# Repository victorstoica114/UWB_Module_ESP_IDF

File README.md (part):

# UWB ESP-IDF

ESP-IDF 6.0.2 firmware for the custom UWB Module V1.0 Rev.B, based on an
ESP32-S3-WROOM-1-N16R8. The same application image runs on every module;
persistent identity and runtime configuration select the role and active
workflow on each board.

The current firmware combines DW3000 positioning, PX1105R GNSS/RTK, BNO085
IMU telemetry, BQ25792 charging, MAX77958 USB-C Power Delivery, authenticated
HTTP OTA/configuration, a browser dashboard, and boot-loop/OTA recovery. The
UWB radio runtimes include Native DS-TWR, FlexTDOA, Passive DS-TWR, calibration,
survey, distance-test, and beacon diagnostics.

Current firmware defaults, before an NVS override is loaded:

| Setting | Default |
| --- | --- |
| Runtime | `uwb_ranging` (Native DS-TWR) |
| UWB | enabled |
| BNO085 | disabled; `2 ms` / 500 Hz requested when enabled |
| PX1105R GNSS | disabled |
| BQ25792 monitor | enabled, nominal 1 Hz refresh |
| MAX77958 monitor | enabled, nominal 1 Hz refresh |
| Wi-Fi logs / binary telemetry | enabled |
| Storage | 16 MB flash, dual 4 MB OTA slots, 8 MB octal PSRAM |

Wi-Fi credentials, the OTA token, and optional NTRIP credentials are read from
the Git-ignored `secrets.h`. Copy `secrets.example.h` as the starting template.
Non-secret defaults live in `components/config`; authenticated runtime
overrides are stored in ESP32 NVS.

## Documentation Map

- Hardware, firmware ownership, boot order, and tasks are documented below in
  [Hardware](#hardware) and [Firmware Architecture](#firmware-architecture).
- UWB modes and packet/timing details start at [App Modes](#app-modes) and
  [UWB Ranging Protocol](#uwb-ranging-protocol). Passive DS-TWR and the clean
  FlexTDOA implementation also have dedicated notes in
  [`docs/PASSIVE_DS_TWR.md`](docs/PASSIVE_DS_TWR.md) and
  [`docs/FLEXTDOA_CLEAN_REIMPLEMENTATION.md`](docs/FLEXTDOA_CLEAN_REIMPLEMENTATION.md).
- Operator controls are grouped under [HTTP Control Surface](#http-control-surface),
  [BNO085 IMU](#bno085-imu), [BQ25792 Battery Charger](#bq25792-battery-charger),
  and [MAX77958 USB-C PD Controller](#max77958-usb-c-pd-controller).
- Build, serial flash, OTA, dashboard, and host-test commands are under
  [Local Workflow, Flashing, and VS Code Tasks](#local-workflow-flashing-and-vs-code-tasks).
- Released ESP32 images are on the
  [GitHub Releases page](https://github.com/victorstoica114/UWB_Module_ESP_IDF/releases),
  while the separately versioned GNSS image is indexed in
  [`PX1105R-firmware/README.md`](PX1105R-firmware/README.md).
- Final reports and their retained evidence bundles are indexed in
  [`reports/README.md`](reports/README.md).
- The parametric enclosure sources, print-ready STL files, STEP exports, and
  assembly notes are under
  [`mechanical/uwb-gps-enclosure/`](mechanical/uwb-gps-enclosure/README.md).

## Hardware

This firmware targets the custom UWB Module V1.0 Rev.B hardware.

| Area | Details |
| --- | --- |
| MCU | ESP32-S3-WROOM-1-N16R8 |
| Flash / PSRAM | 16 MB flash, 8 MB PSRAM |
| USB | Native USB CDC on boot |
| UWB | DW3000/DWM3000 radio path |
| IMU | BNO085 over shared I2C |
| GPS | PX1105R/PX1125R-class GPS path |
| USB-C / PD | MAX77958 |
| Charger | BQ25792 |
| Status LED | GPIO42, active-high |

Active pin mapping lives in `components/config/include/board_config.h`.

| Function | GPIO |
| --- | --- |
| Status LED | `42` |
| Shared I2C SDA / SCL | `9` / `10` |
| BNO085 reset / interrupt | `40` / `15` |
| BQ25792 interrupt / QON command / board PG | `4` / `38` / `5` |
| UWB reset / IRQ / CS / wakeup | `8` / `6` / `48` / `7` |
| SPI MOSI / SCK / MISO | `11` / `12` / `13` |
| GPS enable / RX / TX | `47` / `18` / `17` |
| GNSS correction UART TX | `1` |

### DW3000 SPI Clock

The DWM3000 data sheet specifies a maximum SPI clock of `38 MHz` in mode 0
after OTP boot has completed. ESP32-S3 SPI2 is sourced from the `80 MHz` APB
clock and can generate `40 MHz` exactly. This project deliberately selects
that divider after field validation on all five modules. It is a documented
2 MHz overclock, guarded by an explicit compile-time opt-in and a separate
`38 MHz` data-sheet-limit constant so the exception cannot be accidental.

The driver therefore uses two phases:

1. reset, `DEV_ID` probe, soft reset, OTP reads, and radio configuration at
   `4 MHz`;
2. operational RX/TX traffic requested and realized at `40 MHz`, after eight
   consecutive `DEV_ID` read-backs succeed.

If the operational verification fails, the driver automatically restores the
`4 MHz` device configuration so the module remains reachable. `/status`
exposes the effective value as `uwb_spi_clock_hz`; this is the frequency
reported by the ESP-IDF SPI driver, not only the requested value.

Hardware validation on all five modules, updated 2026-08-05:

| Metric | Result |
| --- | ---: |
| Effective SPI clock, every module | `40 MHz` |
| Pure CI-CR validation window | `35 s` |
| Selected slot / four-anchor frame | `4.80 ms / 19.20 ms` |
| Passive observations | `443-450/s` |
| Telemetry drops | `0` |
| Responder-index balance per anchor | typically `37-39 / 37-39 / 37-39` per second |
| Rejected tag observations | typically `0-1/s` |
| Incoherent anchor timestamps in stable windows | `0` |

The radio test exercises TX-buffer writes, delayed-TX programming, timestamp
and status reads, and RX-buffer reads. It is therefore a stronger link check
than probing `DEV_ID` alone.

## Firmware Architecture

`main/app_main.c` only calls `app_manager_start()`. The application manager
initializes identity and runtime configuration, brings up the recovery/control
plane first, and then starts hardware services and exactly one UWB runtime.

| Component | Responsibility |
| --- | --- |
| `app_manager` | Boot sequencing, status LED, recovery cutoff, and active-runtime selection. |
| `config` | Board pins, compile-time defaults, persistent module identity/antenna delay, and NVS runtime configuration. |
| `boot_guard` | ESP-IDF OTA validation plus RTC-memory crash-loop detection and recovery mode. |
| `wifi_service` | STA scan, connection, reconnect, BSSID/channel diagnostics, and network status. |
| `ota_service` | HTTP server, `/status`, OTA, GNSS update staging, and authenticated configuration endpoints. |
| `wireless_log_service` | TCP mirror of ESP-IDF text logs. |
| `wireless_telemetry_service` | Batched `UWT1` binary sensor, geometry, range, and position streams. |
| `resource_monitor_service` | Bounded RAM, PSRAM, flash, temperature, and per-core CPU diagnostics. |
| `i2c_bus_service` | Shared BNO085 realtime/BQ25792/MAX77958 background arbitration and optional SCL measurement. |
| `bno085_service` | Interrupt-driven accelerometer and GyroRV acquisition, timestamp reconstruction, recovery, rings, and telemetry. |
| `charger_service` | BQ25792 monitoring, decoded status/ADC data, controlled writes, and NVS-backed charger policy. |
| `max77958_service` | MAX77958 status, AP commands, optional direct-HS I2C, PDO/PPS control, and NVS-backed PD policy. |
| `gps_service` | PX1105R power/UART control, NMEA/SkyTraq parsing, 8 Hz setup, moving-base transport, and NTRIP. |
| `gnss_firmware_updater` | Fixed PX1105R loader/image update sequence using ESP32 PSRAM staging. |
| `uwb_dw3000` | DW3000 GPIO/SPI/IRQ ownership and all timing-critical UWB runtime loops. |
| `uwb_ranging_service` | Native DS-TWR positioning entry point. |
| `uwb_distance_test_service` | Two-module five-frame diagnostic DS-TWR entry point. |
| `uwb_calibration_service` | Two- and three-module antenna-delay calibration entry point. |
| `uwb_anchor_survey_service` | Anchor-to-anchor survey entry point. |
| `flextdoa_protocol` | FlexTDOA packet codec, collector, and CFO estimator. |
| `flextdoa_algmin` | FlexTDOA frame aggregation and 2D minimization. |
| `flextdoa_solver_service` | Asynchronous embedded FlexTDOA solver and position publication. |
| `passive_ds_solver_service` | Passive DS batching, dynamic geometry, correlated solve, and position publication. |
| `uwb_mobile_geometry` | Converts GNSS anchor positions into a shared local UWB coordinate frame. |
| `uwb_localization_solver` | Generic tested range/range-difference solver library; it is not the owner of a current runtime loop. |

Repository-level supporting material:

| Path | Contents |
| --- | --- |
| `tools/` | Build/OTA helpers, dashboard, listeners, capture, replay, calibration, and analysis tools. |
| `tests/` | Python host tests and standalone C algorithm/protocol tests. |
| `docs/` | Focused protocol and implementation notes. |
| `firmware_images/` | Retained ESP32 release inputs, stored through Git LFS where configured. |
| `PX1105R-firmware/` | Permanent GNSS firmware index and validated ESP32-assisted update artifacts. |
| `reports/` | Final PDFs plus one self-contained evidence bundle for each report. |
| `mechanical/uwb-gps-enclosure/` | Parametric V4 enclosure source, reference geometry, print-ready STL files, STEP exports, and previews. |
| `PCB/V1.REV.B/` | KiCad source, fabrication, BOM, and placement package. |
| `Schematic/` / `datasheets/` | Exported board schematic and local silicon/reference documents. |
| `reference/` | Migration notes and the intentionally retained legacy GPIO header. |

`components/config/include/board_config.h` is the active board pin map.
Old GPIO naming is kept only under `reference/legacy_headers`.
Old legacy project files and cloned third-party repositories are kept local for
inspiration/debugging and are intentionally ignored by Git.

`components/config/include/app_config.h` holds versioned non-secret application
settings: the default runtime mode, persistent identity provisioning, Wi-Fi
diagnostics/reconnect behavior, wireless-log defaults, OTA-adjacent
service defaults, and optional sensor-test parameters. `components/config/include/uwb_config.h`
holds UWB-only settings: role, source ID override, antenna delay, beacon
smoke-test parameters, and runtime defaults. Runtime overrides are stored in
NVS through `/config/runtime`. Keep Wi-Fi credentials and OTA tokens in
`secrets.h`.

Runtime ownership is intentionally narrow:

- `main/app_main.c` only boots the firmware and calls `app_manager_start()`.
- `components/app_manager/app_manager.c` owns what runs on the board and in
  what order.
- Long-lived workflows live in separate services/components, then are selected
  or sequenced by `app_manager`.

The current boot sequence is also explicit. `app_manager` starts the status LED
and boot guard, loads identity/runtime configuration, then brings up Wi-Fi,
wireless logs, binary telemetry, and the HTTP/OTA server. It schedules stable
boot confirmation only after that recovery/control plane is reachable. A normal
boot then starts the resource monitor, optional GNSS, the selected UWB runtime,
BQ25792, MAX77958, and finally the optional BNO085 service. Recovery mode stops
before that second group and holds the DW3000 in reset.

The application task/core split is kept simple so the UWB loop is isolated from
most Wi-Fi and TCP work:

| Task / service | Core | Notes |
| --- | --- | --- |
| `uwb_dw3000` | 1 | Owns DW3000 init, SPI access, RX/TX, ranging, survey, and calibration loops. |
| `status_led` | 1 | Lightweight GPIO blink task. |
| `boot_guard` | unpinned | Confirms stable boots after Wi-Fi/OTA are online and holds recovery state across resets. |
| `wifi_service` | 0 | Owns Wi-Fi STA connect/reconnect management. |
| `ota_service` / `httpd` | 0 | Starts authenticated OTA, `/status`, and runtime-config HTTP handling. |
| `bno085` | 0 | Interrupt-driven BNO085 accelerometer/GyroRV service; owns realtime priority on the shared I2C bus. |
| `bq25792` | 0 | Low-rate charger monitor; uses background I2C access so BNO085 can win bus arbitration. |
| `max77958` | 0 | Low-rate USB-C PD monitor/config service; also uses background I2C access. |
| `gps` | 0 | PX1105R power, UART parsing, and moving-base integration when runtime-enabled. |
| `gps_ntrip` | unpinned | Optional single NTRIP caster connection owned by the configured module. |
| `flex_algmin` | 0 | FlexTDOA solver worker, created only by that runtime. |
| `passive_ds_solver` | 0 | Passive DS solver worker with its large stack allocated from PSRAM. |
| `resource_monitor` | 0 | Low-priority bounded resource sampling. |
| `wireless_log` | unpinned | Drains the log queue and mirrors logs over TCP; FreeRTOS may run it on either core. |
| `wireless_tel` | 1 | Drains high-rate telemetry into batched TCP writes. |
| short-lived reboot tasks | unpinned | Temporary restart helpers after OTA or runtime-config changes that explicitly require a reboot. |

ESP-IDF also creates internal Wi-Fi, TCP/IP, and event-loop tasks. The HTTP
server task is pinned to core 0 so `/status` and runtime config do not share the
UWB core. The timing-critical UWB transmit instants are still programmed into
the DW3000 with delayed TX, so the radio owns the sub-microsecond timing rather
than the FreeRTOS scheduler.

UWB waits are deliberately yielding. RX/TX waits use the DW3000 IRQ line and
FreeRTOS task notifications when IRQ is enabled, with `vTaskDelay` as the
fallback path. Calibration slot alignment uses the dedicated 1 MHz ESP GPTimer
alarm plus a task notification, so the firmware does not busy-loop while waiting
for the guard window or slot end.

## Boot Recovery

The firmware has two recovery layers so a bad OTA or a crash loop should not
make a module disappear from Wi-Fi permanently.

| Layer | What it handles | Mechanism |
| --- | --- | --- |
| ESP-IDF OTA rollback | A new OTA image crashes or resets before it proves it can boot. | `CONFIG_BOOTLOADER_APP_ROLLBACK_ENABLE` marks a fresh OTA image as `pending_verify`. The app calls `esp_ota_mark_app_valid_cancel_rollback()` only after Wi-Fi and OTA HTTP are online for `APP_BOOT_GUARD_STABLE_DELAY_MS`. If a reset happens first, the bootloader rolls back to the previous valid OTA slot. |
| Local recovery mode | A valid app, serial-flashed app, or bad runtime config keeps rebooting. | `components/boot_guard` stores a small state record in RTC no-init memory. After `APP_BOOT_GUARD_FAILURE_THRESHOLD` unstable resets, the next boot starts only identity/runtime config, Wi-Fi, wireless log, telemetry, and OTA. UWB, GPS, charger, USB-C PD, resource monitor, and BNO085 are skipped. |

Normal boot order is intentionally conservative: Wi-Fi, wireless log, telemetry,
and OTA start before UWB or I2C peripherals. Recovery mode uses the same path but
stops before the risky services and holds the DW3000 in reset.

Task watchdog panic is enabled on purpose. A task watchdog, interrupt watchdog,
panic, generic watchdog, or CPU lockup reset is counted as a recovery failure
even if the previous boot had already been marked stable. This catches runtime
configuration lockups that happen minutes or hours after boot instead of only
early boot loops.

`/status` exposes the recovery state:

| Field | Meaning |
| --- | --- |
| `boot_recovery_mode` | `true` when only the minimal recovery services are running. |
| `boot_guard_failure_count` | Consecutive unstable resets counted in RTC memory. |
| `boot_guard_recovery_threshold` | Failure count that latches recovery mode. |
| `boot_guard_ota_state` | Current OTA state, such as `valid` or `pending_verify`. |
| `boot_guard_pending_verify` | The running app still needs to be marked valid. |
| `boot_guard_last_reset_reason_name` | Last reset reason reported by ESP-IDF. |

Recovery can be cleared after uploading a known-good firmware or runtime config:

```sh
curl -X POST -H "X-OTA-Token: <APP_OTA_PASSWORD>" \
  "http://<module-ip>/config/recovery?clear=1&reboot=1"
```

Important: rollback lives in the bootloader. OTA updates replace only the app
partition, so each module needs one full serial flash after enabling rollback.
After that, future OTA images are protected by the rollback flow.

## HTTP Control Surface

The ESP32 exposes one HTTP control plane after Wi-Fi starts. `GET /` and
`GET /status` are intentionally readable without authentication. Every `POST`
endpoint requires the same header used by OTA:

```text
X-OTA-Token: <APP_OTA_PASSWORD>
```

The password comes from the Git-ignored `secrets.h`. Configuration values are
passed as URL query parameters even though the method is `POST`; an empty body
is valid. For example:

```sh
curl -X POST -H "X-OTA-Token: <APP_OTA_PASSWORD>" \
  "http://<module-ip>/config/runtime?bno085=1&bno085_sample_hz=500"
```

| Method and path | Purpose | Persistence / restart behavior |
| --- | --- | --- |
| `GET /` | Short endpoint and usage summary. | Read-only. |
| `GET /status` | JSON snapshot of identity, boot, UWB, GNSS, IMU, charger, PD, resources, logs, and telemetry. | Read-only. |
| `POST /ota` | Upload an ESP-IDF application image to the inactive OTA slot. | Reboots into the new image; NVS is preserved. |
| `POST /gnss/loader` | Stage the validated PX1105R loader artifact in PSRAM. | Volatile staging step. |
| `POST /gnss/firmware` | Stage the validated PX1105R firmware artifact in PSRAM. | Volatile staging step. |
| `POST /gnss/firmware/run` | Run the fixed GNSS loader/update sequence using the staged artifacts. | Reprograms the GNSS receiver, not the ESP32. |
| `POST /config/antenna-delay` | Stage a calibrated DW3000 antenna delay. | Stored in NVS; applied at radio initialization. |
| `POST /config/runtime` | Change runtime, topology, timing, diagnostics, GNSS, UWB, or BNO085 configuration. | Stored in NVS; some fields apply live or by UWB hot switch, others require `reboot=1`. |
| `POST /config/recovery` | Clear the local boot-guard latch and optionally reboot. | Updates boot-guard state. |
| `POST /config/charger` | Refresh or configure the BQ25792. | High-level policy is stored in NVS; raw writes are not. |
| `POST /config/max77958` | Refresh, inspect, or configure MAX77958 USB-C/PD behavior. | Selected high-level policy is stored in NVS; diagnostic operations and raw writes are not. |

Boolean charger/PD parameters accept `1/0`, `true/false`, `on/off`, and
`yes/no`. Runtime booleans accept `1/0`, `true/false`, and `on/off`. Invalid,
out-of-range, incomplete, or unauthenticated requests are rejected; callers
should check both the HTTP status and the JSON response instead of assuming a
write succeeded. The exact BNO085, charger, and PD command tables are in their
respective sections below.

## 3D-Printed Enclosure

The complete modular V4 enclosure is versioned under
[`mechanical/uwb-gps-enclosure/`](mechanical/uwb-gps-enclosure/README.md). It
includes the CadQuery generator, input reference geometry, validation manifest,
assembly STEP model, rendered previews, and eight print-oriented STL parts.

For printing, use the files ending in `_PRINT.stl` from
[`mechanical/uwb-gps-enclosure/exports/`](mechanical/uwb-gps-enclosure/exports/).
The enclosure README documents the required inserts, magnets, screws, print
orientation, and assembly order.

The binary CAD, mesh, reference-image, and preview assets are stored through
Git LFS. The source was imported from the validated V4 enclosure revision
`7e0be77` of
[`AlexandruPalacean/uwb-gps-enclosure`](https://github.com/AlexandruPalacean/uwb-gps-enclosure).

## PCB Package

The hardware package is versioned with the firmware so the board definition and
software assumptions stay together.

| Path | Purpose |
| --- | --- |
| `PCB/V1.REV.B/Kicad project/` | Editable KiCad project and local symbols/footprints |
| `PCB/V1.REV.B/Gerber/Gerber.zip` | Fabrication archive |
| `PCB/V1.REV.B/BOM/` | BOM exports |
| `PCB/V1.REV.B/PickAndPlace/` | Assembly placement files |
| `Schematic/UWB_V1.0_Rev.B.pdf` | Exported schematic PDF |

PCB preview:

## Released Firmware Images

ESP32 images are published as one GitHub Release per firmware version, ordered
from the oldest retained version to the newest. Each release keeps only the
artifacts needed to install that version; intermediate ESP-IDF build trees are
not release artifacts. The retained source images under `firmware_images/` are
tracked with Git LFS.

The release asset names have distinct purposes:

| Asset | Use |
| --- | --- |
| `uwb_ota.bin` | OTA through `POST /ota` or `tools/ota_upload.py`; preserves NVS. |
| `uwb_full_flash.bin` | Complete serial recovery/provisioning image written at offset `0x0`; may replace NVS and therefore require identity, runtime, and antenna-delay provisioning again. |
| Per-partition `.bin` files, when present | Low-level ESP-IDF/esptool recovery and diagnosis. Use the offsets documented with that release. |

The current retained ESP32 sequence starts at
`firmware-20260804-222730-flextdoa-accuracy` and ends at
`firmware-20260813-190254-native-uwb-only`. Use the
[GitHub Releases page](https://github.com/victorstoica114/UWB_Module_ESP_IDF/releases)
as the canonical download location rather than copying binaries from an old
build directory.

PX1105R firmware is versioned independently so the same GNSS payload is not
duplicated in every ESP32 release. The permanent entry point is
[`PX1105R-firmware/README.md`](PX1105R-firmware/README.md), which links the
dedicated `gps-px1105r-01.07.33` release and records the validated artifacts and
ESP32-assisted update command.

## App Modes

The expected UWB workflow split is:

1. `APP_RUNTIME_MODE_UWB_BEACON_SMOKE`: current random beacon TX/RX smoke test
   in `components/uwb_dw3000`.
2. `APP_RUNTIME_MODE_UWB_ANTENNA_DELAY_CALIBRATION`: antenna delay
   calibration entry point in `components/uwb_calibration_service`.
3. `APP_RUNTIME_MODE_UWB_DISTANCE_TEST`: current two-module DS-TWR ruler check
   entry point in `components/uwb_distance_test_service`.
4. `APP_RUNTIME_MODE_UWB_RANGING`: current 4-anchor plus 1-tag DS-TWR
   ranging runtime in `components/uwb_ranging_service`. The first configured
   anchor coordinates the slots, anchors initiate, and the tag responds/logs
   tag-anchor distances for the dashboard.
5. `APP_RUNTIME_MODE_UWB_ANCHOR_SURVEY`: anchor-to-anchor survey/runtime
   diagnostics in `components/uwb_anchor_survey_service`.
6. `APP_RUNTIME_MODE_UWB_FLEX_TDOA`: experimental FlexTDOA runtime. Anchors
   rotate as short-slot initiators, continuously refresh live anchor geometry,
   and the tag only listens on UWB while sending range-difference observations
   to the dashboard over Wi-Fi logs.
7. `APP_RUNTIME_MODE_UWB_PASSIVE_DS_TWR`: project-specific three-frame
   anchor-to-anchor DS-TWR with receive-only tags. It provides independent
   Fast Star and Robust Rotating schedules; see
   [`docs/PASSIVE_DS_TWR.md`](docs/PASSIVE_DS_TWR.md). The surveyed-square
   calibration data and 1.89 cm offline RMSE result are preserved in
   [`reports/bundles/passive_ds_known_geometry_20260727`](reports/bundles/passive_ds_known_geometry_20260727/README.md).

The beacon smoke mode, distance-test mode, antenna-delay calibration workflows,
anchor survey, multi-anchor ranging, and experimental FlexTDOA runtimes are
implemented for the current lab workflow.

`APP_RUNTIME_MODE` remains the firmware default. The effective runtime mode and
common test parameters can be overridden at runtime through NVS using the
authenticated `/config/runtime` HTTP endpoint.

### Hot Protocol Switching

The Position tab switches directly between Native DS-TWR, FlexTDOA, and Passive
DS-TWR through `/config/runtime?...&hot_switch=1`. A successful hot switch:

- persists the selected mode in NVS;
- lets the active UWB loop leave at a safe protocol boundary;
- stops the active UWB timers and resets the solver state;
- resets and reconfigures only the DW3000; and
- keeps Wi-Fi, HTTP, wireless logs, and binary telemetry running.

The supervisor restores the 4 MHz DW3000 boot SPI rate for the radio reset and
returns to the verified datasheet-compliant operational rate after
initialization. If radio
initialization fails, the firmware falls back to a full ESP32 restart.

Hot switching is deliberately limited to a mode-only transition among these
three positioning runtimes. Changes to module topology, tag/anchor IDs, channel,
radio settings, timing parameters, diagnostics, calibration, or survey modes
still follow the normal reboot path. The `/status` response exposes
`uwb_runtime_switching`, `uwb_runtime_switch_count`, and
`uwb_last_runtime_switch_ms` so the dashboard can distinguish a short radio
transition from an offline module.

The five-module live test on 2026-07-27 produced:

| Transition | HTTP acknowledgement | All modules UWB-ready | First complete live data |
| --- | ---: | ---: | ---: |
| Native DS-TWR -> FlexTDOA | 0.101 s | 0.773 s | 0.784 s |
| FlexTDOA -> Passive DS-TWR | 0.105 s | 0.623 s | 0.932 s |
| Passive DS-TWR -> Native DS-TWR | 0.083 s | 0.764 s | 0.814 s tag ranges; 2.115 s all six anchor pairs |

The measured DW3000 reinitialization time was 449-481 ms. ESP32 boot counters
did not change during any transition.

## UWB Ranging Protocol

The active ranging implementation is based on Double-Sided Two-Way Ranging
(DS-TWR). Position ranging uses exactly the three native UWB frames: `POLL`,
`RESP`, and `FINAL`.

| Frame | Direction | Purpose |
| --- | --- | --- |
| `POLL` | tag -> anchor | 10-byte protocol header that starts one ranging exchange. |
| `RESP` | anchor -> tag | 10-byte protocol header that provides the responder turnaround. |
| `FINAL` | tag -> anchor | 35 bytes: header plus the tag's `POLL TX`, `RESP RX`, and scheduled `FINAL TX` timestamps. |

The anchor combines the timestamps carried in `FINAL` with its own `POLL RX`,
`RESP TX`, and `FINAL RX` hardware timestamps and calculates the distance
locally. It reports the result through Wi-Fi, not through an additional UWB
frame. The separate distance-test and calibration runtimes retain their
five-frame diagnostic exchange for bidirectional verification.

### Runtime Shape

The same firmware image runs on every module. At boot, each board reads its
persistent module ID and runtime config from NVS.

| Module ID | Normal ranging behavior |
| --- | --- |
| `1` | Tag / initiator; ranges each configured anchor in order |
| `2` | Anchor / responder |
| `3` | Anchor / responder |
| `4` | Anchor / responder |
| `5` | Anchor / responder |

`APP_RUNTIME_MODE_UWB_RANGING` is tag-initiated. The tag owns the complete
frame schedule and starts one native DS-TWR exchange in every anchor slot.
There is no coordinator, `RANGING_CMD`, `REPORT`, or `REPORT2`. Each responding
anchor calculates the range after `FINAL` and returns it in a one-shot UWB
`RESULT` packet. The ESP32 tag solves every coherent four-anchor frame and
publishes the range and raw independent-frame position over Wi-Fi. The
dashboard displays that result and the host tools can independently replay it
for RTK comparison; no temporal position filter is applied.

Native DS protocol version 2 protects every packet with CRC-16/CCITT-FALSE.
This application-level CRC also detects payload corruption on the DW3000-to-ESP
SPI path after the radio has already accepted the over-the-air frame check.

The tag schedules anchors sequentially:

```text
round N

tag 1 -> anchor 2
tag 1 -> anchor 3
tag 1 -> anchor 4
tag 1 -> anchor 5

wait ranging_round_gap_ms
round N + 1
...
```

The important timing parameters are exposed by `/status`, can be changed with
`/config/runtime`, and are also available in the dashboard:

| Name | Default / lab value | Meaning |
| --- | ---: | --- |
| `ranging_slot_ms` | `10 ms` | Time budget for one native four-packet exchange. |
| `ranging_round_gap_ms` | `4 ms` | Gap after all anchor slots in one frame. |
| `ranging_rx_slice_ms` | `100 ms` | RX window used by idle anchor responders. |
| `ranging_rx_timeout_ms` | `5 ms` | Maximum wait for the expected `RESP`, `FINAL`, or `RESULT`. |
| `ranging_resp_delay_ms` | `2 ms` | Delayed TX offset from `POLL RX` to `RESP TX`; also used from `FINAL RX` to `RESULT TX`. |
| `ranging_final_delay_ms` | `2 ms` | Delayed TX offset from `RESP RX` to `FINAL TX`. |
| `ranging_auto_rx_delay_uus` | `500 UUS` | DW3000 hardware delay before auto-RX opens after TX. |

These values have their own NVS keys and dashboard profiles. Changing them does
not modify FlexTDOA, distance-test, calibration, or anchor-survey timing. The
tag uses a high-resolution host timer for slot and frame-gap boundaries, so
profiles are not rounded to the 10 ms FreeRTOS tick. Native DS-TWR timing is
copied when its UWB task starts. Timing-only changes can request an in-place
UWB hot switch, which cleanly restarts the radio runtime while Wi-Fi, GPS and
the ESP32 stay online. For four anchors, the default frame is
`4 * 10 + 4 = 44 ms`.

The selected field profile is a 10 ms slot, 4 ms frame gap, 100 ms idle-anchor
RX slice, 5 ms expected-frame timeout, and 2 ms for each delayed transmission.
In a 180-second channel-9 run it completed 15,138 of 15,183 exchanges
(`99.704%`), produced 20.82 raw positions/s, and measured 1.80 cm RMSE and
3.07 cm P95 against stabilized RTK, without position filtering. A 42 ms frame
raised throughput to 21.45 positions/s but reduced completion to 99.357%; a
43 ms frame reached 21.12 positions/s at 99.491%. The 44 ms profile is the
recommended robustness/throughput tradeoff. The 64 ms and 100 ms profiles
remain available as intermediate and conservative fallbacks.

### FlexTDOA Runtime

`APP_RUNTIME_MODE_UWB_FLEX_TDOA` is the active pure CI-CR radio protocol with a
radio-passive tag.
The tag does not call any UWB TX function in this mode. It only receives anchor
frames, records its own RX timestamps, feeds the local AlgMin solver, and sends
compact binary range-difference and position telemetry to the dashboard.

FlexTDOA roles are derived from the configured anchor list. Every module in
that list is an anchor; every participating module outside it is a passive tag
and labels telemetry with its own module ID. This permits multiple passive tags
without adding radio slots. An ID must never appear in both `Anchor IDs` and
`Tag IDs`; the dashboard rejects that configuration. For example, with five
modules, anchors `2,3,4` can be combined with tags `1,5`.

The current firmware is aligned with the FlexTDOA paper at the radio slot level:
one anchor is the initiator in a slot, it broadcasts one request, and `K`
responders answer in ordered response subslots. With four configured anchors,
`K = 3` and a full frame has four initiator slots. The tag remains passive and
derives range-difference observations only from the packets it hears.

With anchors `2,3,4,5`, the changing-initiator/changing-responder schedule is:

```text
round 0
  slot 0: A2 requests, responders A3,A4,A5
  slot 1: A3 requests, responders A4,A5,A2
  slot 2: A4 requests, responders A5,A2,A3
  slot 3: A5 requests, responders A2,A3,A4

round 1
  slot 0: A2 requests, responders A4,A5,A3
  slot 1: A3 requests, responders A5,A2,A4
  slot 2: A4 requests, responders A2,A3,A5
  slot 3: A5 requests, responders A3,A4,A2
```

The responder list rotates from the absolute 32-bit slot ID, `slot_id % K`.
Consequently both the initiator and the first responder change at every slot,
including between adjacent slots in the same frame. This implements the
paper's CI-CR scheme without holding one response order for an entire frame.

The active FlexTDOA frame set is:

| Frame | Direction | Purpose |
| --- | --- | --- |
| `FLEX_TDOA_REQ` | initiator -> broadcast | Paper request. Carries the 32-bit slot ID, responder count/order, zero processing delay, and one previous TWR result from this initiator. |
| `FLEX_TDOA_RESP` | responder -> broadcast | Paper response. Carries the same slot ID, measured reply delay, and one previous TWR result from this responder. Initiator and responder index are reconstructed from CI-CR plus the source ID. |

Both packet types use the common Figure 3 tail: processing time, previous TWR
responder ID, previous TWR distance, and previous measurement slot. The local
transport header already carries message type, source ID, and sequence, while
the destination list remains variable-length. Every anchor cycles through its
own directed TWR cache so a repeatedly refreshed pair cannot starve the other
pairs. The parser temporarily accepts the older local request/response layout
to keep a parallel OTA rollout operational.

There is no separate coordinator command in the active protocol. After two
seconds of radio silence, the first configured anchor bootstraps slot `0`.
Every anchor reconstructs the TDMA phase from valid request packets. Responses
carry the full 32-bit slot ID and can recover a follower that missed the
request; a directly received request remains the authoritative phase reference
for that slot. Each node schedules only its own next initiator slot, and later
requests continually correct local clock drift.

The topology is represented by the same `N/K/M` parameters used in the paper:

| Field | Meaning | Firmware range |
| --- | --- | --- |
| `N` | Ordered anchor ID list. | `3..10` anchors |
| `K` | Number of responders selected for each request. | `1..N-1` |
| `M` | Number of initiator slots in the repeating frame. | `1..10` slots |
| responder mask | Anchors allowed to respond in one slot; CI-CR rotates the selected `K` through this pool. | one `N`-bit mask per slot |

These values are editable under `UWB Settings > FlexTDOA Network`. Applying a
new topology increments a 32-bit configuration generation and stores it in NVS.
During the three-second startup configuration phase, anchors, the tag, and a
node removed from the new topology can all broadcast their versioned config.
Nodes accept only a newer generation, persist it, and restart their local UWB
state. While the network is running, reception of a newer config causes the
same controlled rebuild. This is the distributed propagation and recovery
path; normal slot synchronization still comes from `REQ/RESP`, not from a
separate periodic synchronization packet.

The versioned fixed-geometry transport remains for backward compatibility with
older captures and deployments. The current positioning workflow clears that
legacy state and does not freeze coordinates: live anchor ranges continuously
drive the embedded and dashboard geometry solvers.

#### FlexTDOA Slot Timing

The CI-CR slot keeps the structure of equation (20) from the paper. Its timing
terms are runtime parameters persisted in NVS and propagated over UWB, so each
tested combination is kept as a named frame-length profile in the dashboard:

```text
t_slot = guard + request_subslot + request_process
       + K * response_subslot
       + K * response_process_per_responder
```

For four anchors, `K = 3`, the dashboard exposes the two field-validated
profiles plus the exact equation (20) paper reference:

| Profile | Guard | REQ | Process REQ | 3 x RESP | 3 x Process RESP | Slot | Frame | Frame rate |
| --- | ---: | ---: | ---: | ---: | ---: | ---: | ---: | ---: |
| `32.20 ms Field Fast` | `250 us` | `2000 us` | `250 us` | `2550 us` | `3000 us` | `8.050 ms` | `32.200 ms` | `31.06 Hz` |
| `34.00 ms Field Stable` | `250 us` | `2000 us` | `250 us` | `3000 us` | `3000 us` | `8.500 ms` | `34.000 ms` | `29.41 Hz` |
| `20.20 ms Paper Reference` | `250 us` | `2000 us` | `250 us` | `750 us` | `1800 us` | `5.050 ms` | `20.200 ms` | `49.50 Hz` |

`32.20 ms Field Fast` is the firmware default. A clean 120 s channel-9 run on
all five deployed modules produced `30.02` independent positions/s, `2.924%`
effective slot loss, zero new delayed-TX errors, `2.03 cm` RMSE and `3.58 cm`
P95 against the static RTK reference, with no position filter. The
`34.00 ms Field Stable` profile remains available as the conservative control.
The paper reference is kept exact for protocol comparison, but its `250 us`
response spacing does not provide enough margin for the complete ESP32-S3
field workload.

For the selected field profile, one slot is:

```text
250 + 2000 + 250 + 3*850 + 3*1000 = 8050 us
```

The selected responder transmits using DW3000 delayed TX from the request RX
timestamp. For the selected field profile:

```text
RESP[0] = REQ_RX + 2250 us
RESP[1] = REQ_RX + 3100 us
RESP[2] = REQ_RX + 3950 us

four-anchor frame = 4 * 8050 us = 32.20 ms
frame rate        = 31.06 frames/s theoretical
measured rate     = 30.02 complete positions/s
```

The responder does not read `SYS_TIME` to turn that relative delay into an
absolute radio timestamp. It combines the already-read request RX timestamp
with the relative delay, writes that target to `DX_TIME`, and issues the native
DW3000 `CMD_DTX` fast command. The reply interval
carried in `FLEX_TDOA_RESP` is derived from the same quantized delayed-TX target,
including TX antenna delay, so the tag subtracts the interval that the radio
actually used rather than an ideal host-side delay.

FlexTDOA RX timestamps also avoid a per-frame `SYS_TIME` reference. The DW3000
double-buffer diagnostic set exposes the low 32 bits of `RX_TIME` reliably, and
adjacent FlexTDOA packets are much closer than the approximately `67 ms` wrap
period of those 32 bits. Firmware therefore extends each low word from the
previous RX timestamp by signed continuity. A hardware diagnostic run found
that the nominal fifth timestamp byte in the buffered metadata was occasionally
incoherent (`21` mismatches in about `18,975` comparisons on M1), so trusting
that byte directly would be less robust than continuity.

One `SYS_TIME` read seeds the 40-bit epoch when the first FlexTDOA packet is
received. A new seed is used only as a recovery action after more than `30 ms`
without a received packet, where low-word continuity would become ambiguous.
There is no periodic or per-frame `SYS_TIME` read in the continuous FlexTDOA
path. Full `SYS_TIME` reads remain in generic DS-TWR timestamp reconstruction
and delayed-TX failure diagnostics; they are not part of the normal FlexTDOA
slot.

The request RX timestamp marks the radio timing reference near the beginning of
the received frame. The field profile reserves a `2000 us` request subslot and
a `250 us` request-processing term before the first response. Together they
cover packet airtime, SPI decode, RX double-buffer release, and delayed-TX
arming. `K * response_process` is the paper's
aggregate response-processing budget, not extra spacing between responses.
The configured quiet guard ends the slot before the next request.

For a slot where `A3` is the initiator:

```text
A3 initiator                  A4/A5/A2 responders             passive tag
 t=0.00 ms  REQ ------------------------>|------------------------> RX REQ
 t=2.25 ms  <---------------- RESP[0] A4 |------------------------> RX RESP
 t=3.10 ms  <---------------- RESP[1] A5 |------------------------> RX RESP
 t=3.95 ms  <---------------- RESP[2] A2 |------------------------> RX RESP
 t=8.05 ms  next initiator request ------|------------------------> next slot
```

The ESP task wakes before its own next request and programs delayed TX. This
preparation lead is local only and adds no airtime. A longer `5000 us` lead was
rejected in hardware tests because it stopped reception before the preceding
slot completed. Delayed responses use the processing budget selected by the
active profile; a rejected or late command is reported explicitly instead of
leaking into the next slot.

The passive tag computes the paper TDOA observation:

```text
diff_dtu = (RESP_RX_tag - REQ_RX_tag)
         - responder_reply_dtu_corrected
         - anchor_anchor_tof_dtu
```

`responder_reply_dtu_corrected` uses the instantaneous DW3000
carrier-integrator clock ratio from that response. `anchor_anchor_tof_dtu`
comes from the cached
anchor-anchor distance learned from the Figure 3 piggyback stream. The latest
directed measurement of either orientation is used until the pair has a newer
value.

No median, moving average, or position filter is applied to the passive tag's
FlexTDOA observations in firmware. Firmware only rejects structurally invalid
observations: mismatched `slot_id`/responder index, missing CIA clock data, or
an RX timestamp outside the current slot. Position solving and any future
estimator are deliberately kept outside this radio validation.

#### FlexTDOA Alignment Audit

| Paper requirement | Firmware state |
| --- | --- |
| Passive DL-TDOA tag | Implemented. The tag only receives `FLEX_TDOA_REQ/RESP`. |
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
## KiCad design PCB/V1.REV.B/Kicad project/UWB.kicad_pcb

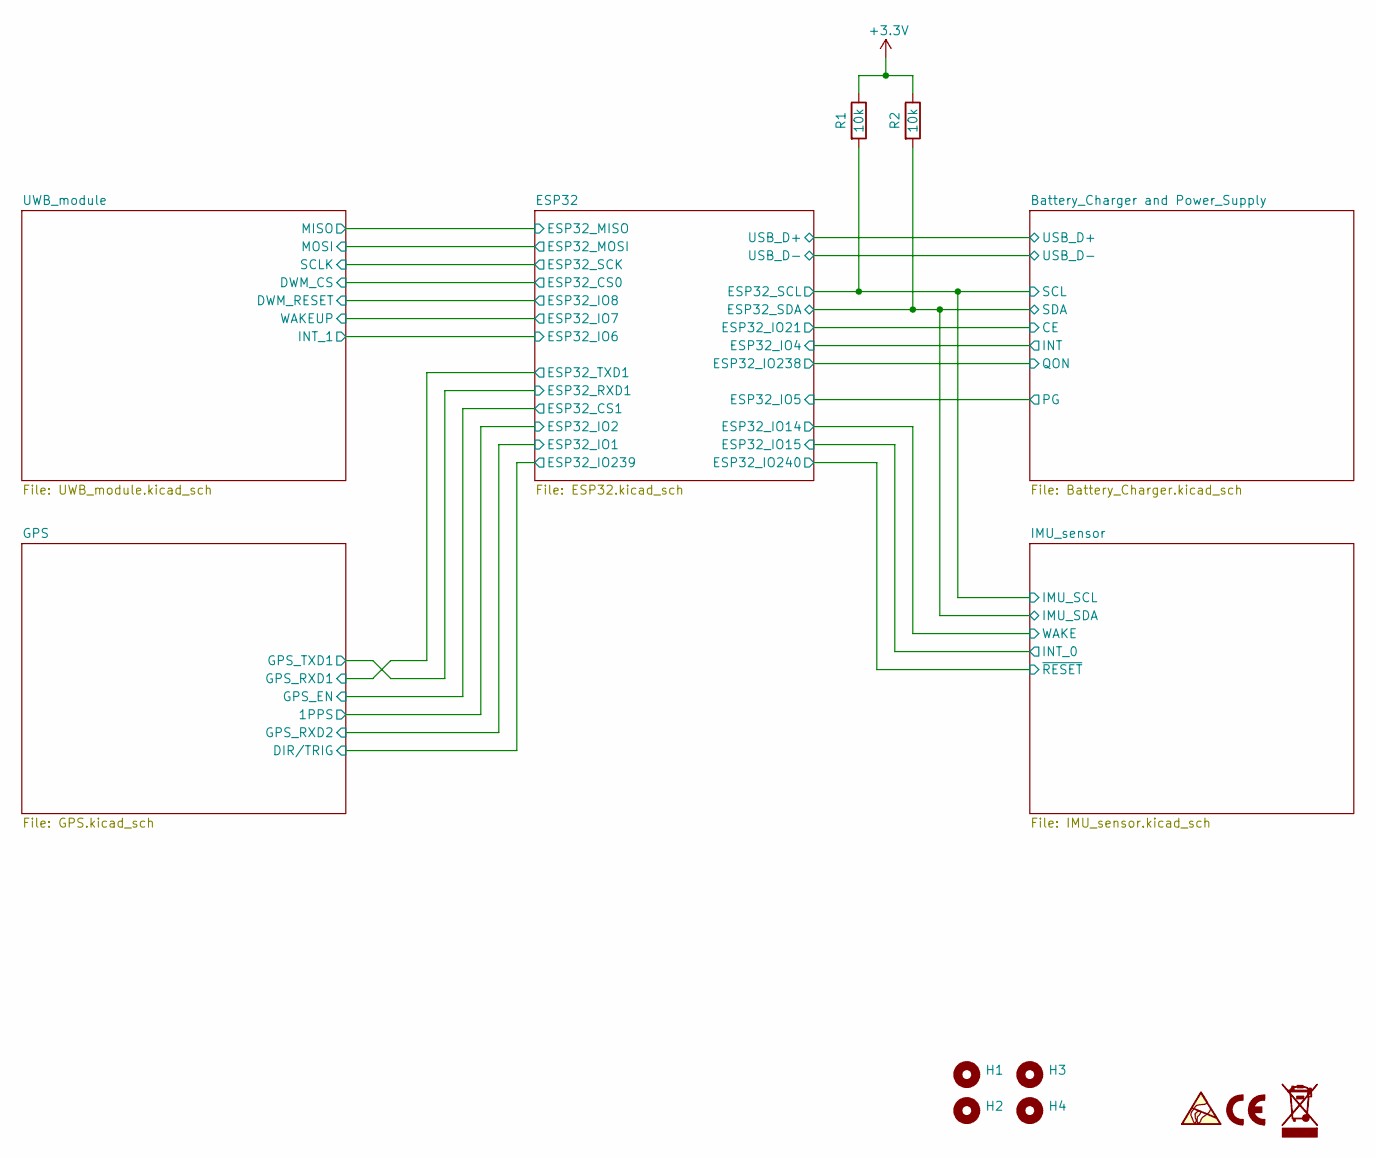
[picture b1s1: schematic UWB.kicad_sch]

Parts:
G1: LOGO; CE-Logo_8.5x6mm_SilkScreen
G2: LOGO; WEEE-Logo_4.2x6mm_SilkScreen
H1, H2, H3, H4: MountingHole; MountingHole_3.2mm_M3
R1, R2: 10k; R_0603_1608Metric; Mfr. part number CR0603-FX-1002ELF; JLCPCB Part C25804
SYM1: SYM_ESD_Small; ESD-Logo_6.6x6mm_SilkScreen

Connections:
+3.3V: R1.1, R2.1; also elsewhere on the board
/Battery_Charger and Power_Supply/SCL: R1.2; also elsewhere on the board
/Battery_Charger and Power_Supply/SDA: R2.2; also elsewhere on the board

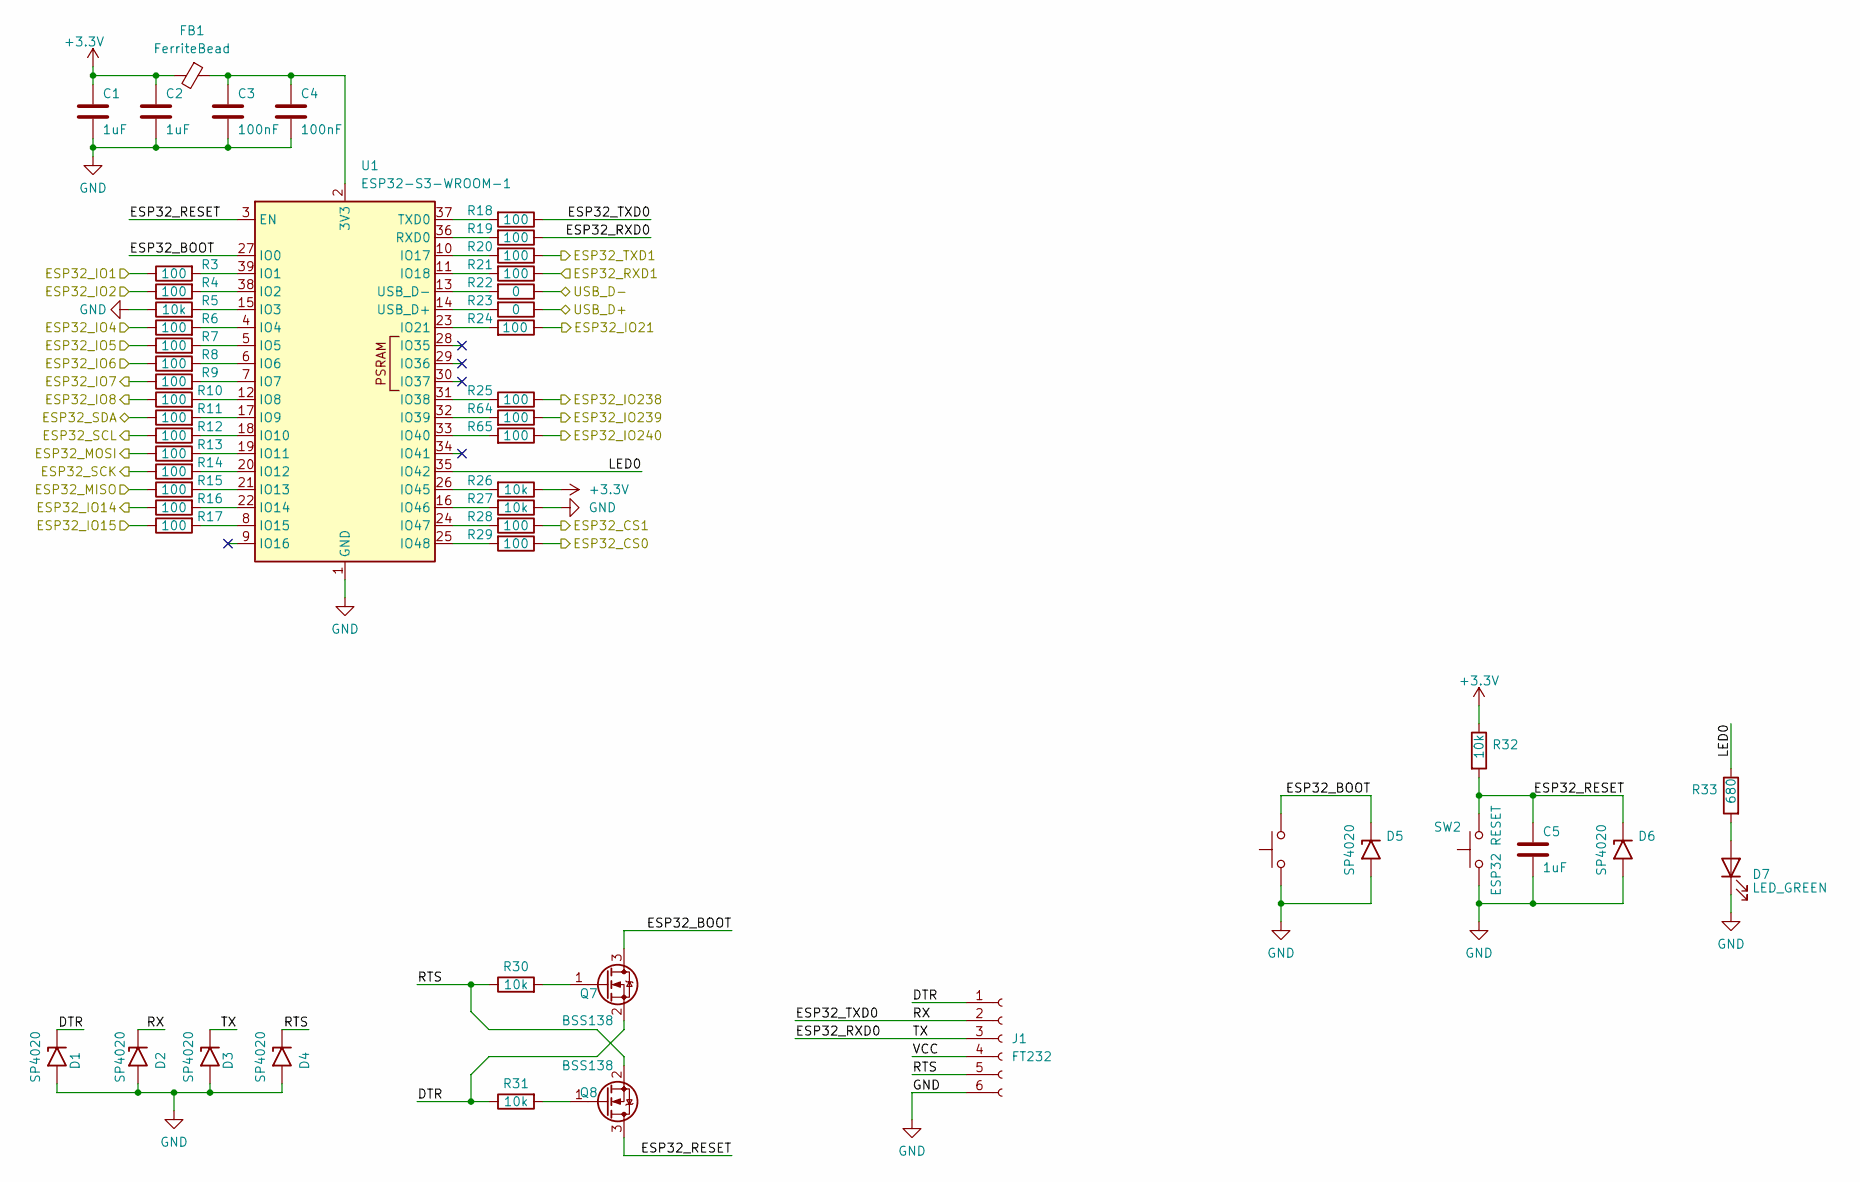
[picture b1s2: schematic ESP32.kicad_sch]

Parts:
C1, C2, C5: 1uF; C_0603_1608Metric; Mfr. part number 885012206052; JLCPCB Part C15849
C3, C4: 100nF; C_0603_1608Metric; Mfr. part number 06035C104KAZ4A; JLCPCB Part C14663
D1, D2, D3, D4, D5, D6: SP4020; D_SOD-323; Mfr. part number SP4020-01FTG-C; JLCPCB Part C126842
D7: LED_GREEN; LED_0603_1608Metric; Mfr. part number 150060VS75000; JLCPCB Part C22371297
FB1: FerriteBead; L_0805_2012Metric; Mfr. part number BLM21SP601SN1D; JLCPCB Part C3716677
J1: FT232; PinSocket_1x06_P2.54mm_Vertical; Mfr. part number 215297-6; JLCPCB Part C8690
Q7, Q8: BSS138; SOT-23; Mfr. part number BSS138; JLCPCB Part C5224261
R3, R4, R6, R7, R8, R9, R10, R11, R12, R13, R14, R15, R16, R17, R18, R19, R20, R21, R24, R25, R28, R29, R64, R65: 100; R_0603_1608Metric; Mfr. part number RE0603FRE07330RL; JLCPCB Part C22775
R5, R26, R27, R30, R31, R32: 10k; R_0603_1608Metric; Mfr. part number CR0603-FX-1002ELF; JLCPCB Part C25804
R22, R23: 0; R_0603_1608Metric; Mfr. part number RC0603FR-130RL; JLCPCB Part C21189
R33: 680; R_0603_1608Metric; Mfr. part number CRGCQ0603F680R; JLCPCB Part C23228
SW1: ESP32 BOOT; SW_Push_1P1T_NO_CK_KMR2; Mfr. part number PTS815SJM250SMTR LFS; JLCPCB Part C99271
SW2: ESP32 RESET; SW_Push_1P1T_NO_CK_KMR2; Mfr. part number PTS815SJM250SMTR LFS; JLCPCB Part C99271
U1: ESP32-S3-WROOM-1; Mfr. part number ESP32-S3-WROOM-1-N16R8; JLCPCB Part C2913202

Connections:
+3.3V: C1.1, C2.1, FB1.2, R26.1, R32.1; also elsewhere on the board
/Battery_Charger and Power_Supply/INT: R6.1; also elsewhere on the board
/Battery_Charger and Power_Supply/PG: R7.1; also elsewhere on the board
/Battery_Charger and Power_Supply/QON: R25.1; also elsewhere on the board
/Battery_Charger and Power_Supply/SCL: R12.1; also elsewhere on the board
/Battery_Charger and Power_Supply/SDA: R11.1; also elsewhere on the board
/Battery_Charger and Power_Supply/USB_D+: R23.1; also elsewhere on the board
/Battery_Charger and Power_Supply/USB_D-: R22.1; also elsewhere on the board
/ESP32/DTR: D1.1 (A1), J1.1, Q7.2 (S), R31.1
/ESP32/ESP32_BOOT: D5.1 (A1), Q7.3 (D), SW1.2, U1.27 (IO0)
/ESP32/ESP32_CS0: R29.1; also elsewhere on the board
/ESP32/ESP32_CS1: R28.1; also elsewhere on the board
/ESP32/ESP32_IO1: R3.1; also elsewhere on the board
/ESP32/ESP32_IO2: R4.1; also elsewhere on the board
/ESP32/ESP32_IO8: R10.1; also elsewhere on the board
/ESP32/ESP32_IO14: R16.1; also elsewhere on the board
/ESP32/ESP32_IO15: R17.1; also elsewhere on the board
/ESP32/ESP32_IO21: R24.1
/ESP32/ESP32_MISO: R15.1; also elsewhere on the board
/ESP32/ESP32_MOSI: R13.1; also elsewhere on the board
/ESP32/ESP32_RESET: C5.1, D6.1 (A1), Q8.3 (D), R32.2, SW2.2, U1.3 (EN)
/ESP32/ESP32_RXD0: D3.1 (A1), J1.3, R19.1
/ESP32/ESP32_RXD1: R21.1; also elsewhere on the board
/ESP32/ESP32_SCK: R14.1; also elsewhere on the board
/ESP32/ESP32_TXD0: D2.1 (A1), J1.2, R18.1
/ESP32/ESP32_TXD1: R20.1; also elsewhere on the board
/ESP32/LED0: R33.1, U1.35 (IO42)
/ESP32/RTS: D4.1 (A1), J1.5, Q8.2 (S), R30.1
/ESP32/VCC: J1.4
/GPS/DIR/TRIG: R64.1; also elsewhere on the board
/IMU_sensor/~RESET: R65.1; also elsewhere on the board
/UWB_module/IRQ/GPIO8: R8.1; also elsewhere on the board
/UWB_module/WAKEUP: R9.1; also elsewhere on the board
GND: C1.2, C2.2, C3.2, C4.2, C5.2, D1.2 (A2), D2.2 (A2), D3.2 (A2), D4.2 (A2), D5.2 (A2), D6.2 (A2), D7.1 (K), J1.6, R5.1, R27.1, SW1.1, SW2.1, U1.1 (GND), U1.40 (GND), U1.41 (GND); also elsewhere on the board
unnamed: D7.2 (A), R33.2
unnamed: Q7.1 (G), R30.2
unnamed: Q8.1 (G), R31.2
unnamed: C3.1, C4.1, FB1.1, U1.2 (3V3)
unnamed: R3.2, U1.39 (IO1)
unnamed: R4.2, U1.38 (IO2)
unnamed: R5.2, U1.15 (IO3)
unnamed: R6.2, U1.4 (IO4)
unnamed: R7.2, U1.5 (IO5)
unnamed: R8.2, U1.6 (IO6)
unnamed: R9.2, U1.7 (IO7)
unnamed: R10.2, U1.12 (IO8)
unnamed: R11.2, U1.17 (IO9)
unnamed: R12.2, U1.18 (IO10)
unnamed: R13.2, U1.19 (IO11)
unnamed: R14.2, U1.20 (IO12)
unnamed: R15.2, U1.21 (IO13)
unnamed: R16.2, U1.22 (IO14)
unnamed: R17.2, U1.8 (IO15)
unnamed: R20.2, U1.10 (IO17)
unnamed: R21.2, U1.11 (IO18)
unnamed: R24.2, U1.23 (IO21)
unnamed: R25.2, U1.31 (IO38)
unnamed: R64.2, U1.32 (IO39)
unnamed: R65.2, U1.33 (IO40)
unnamed: R26.2, U1.26 (IO45)
unnamed: R27.2, U1.16 (IO46)
unnamed: R28.2, U1.24 (IO47)
unnamed: R29.2, U1.25 (IO48)
unnamed: R19.2, U1.36 (RXD0)
unnamed: R18.2, U1.37 (TXD0)
unnamed: R23.2, U1.14 (USB_D+)
unnamed: R22.2, U1.13 (USB_D-)

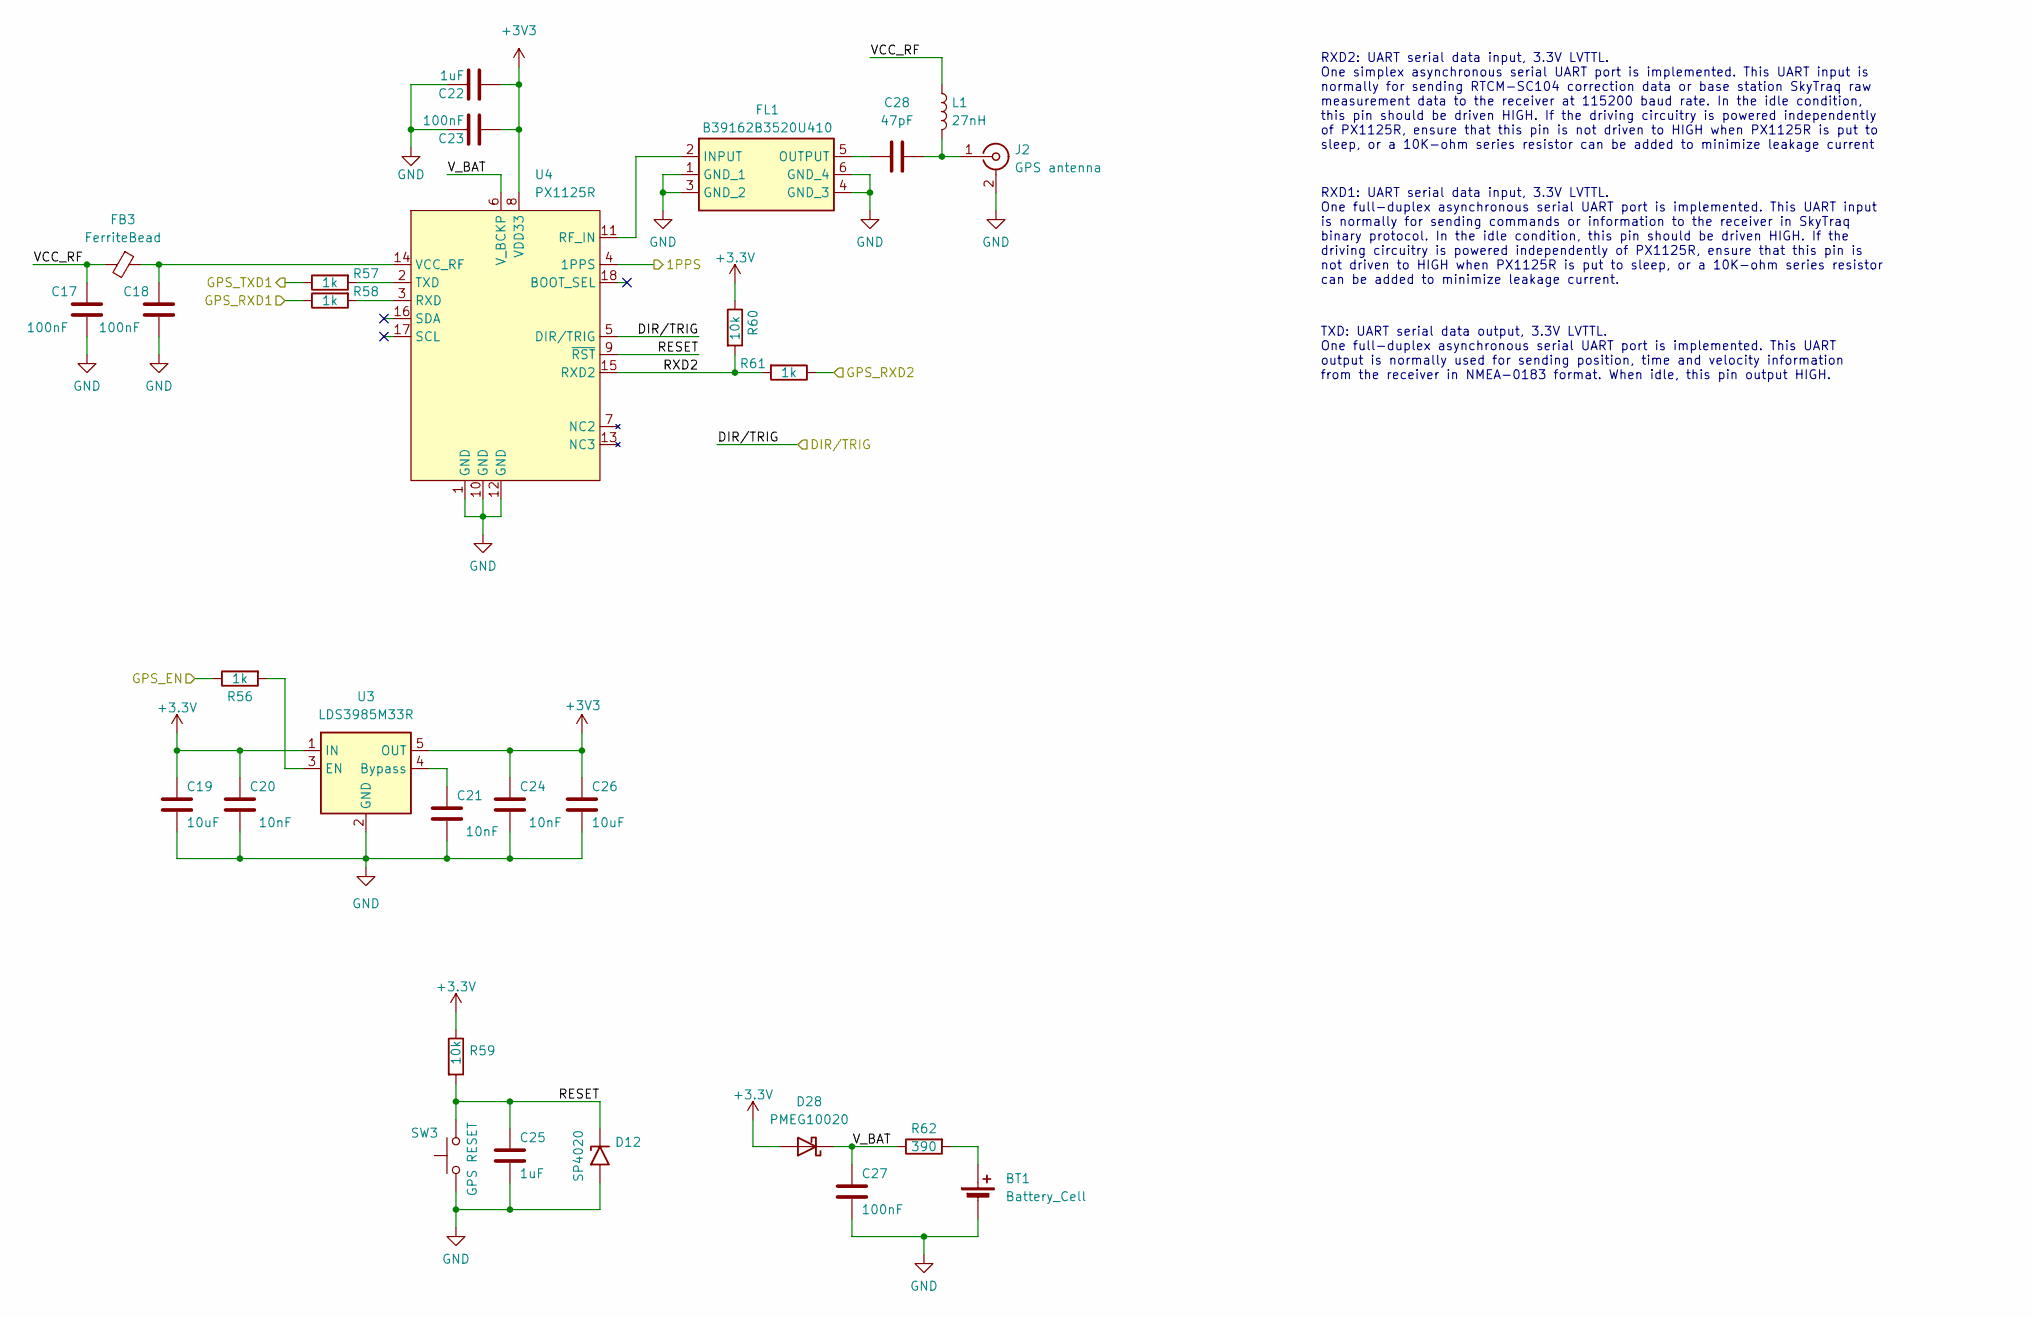
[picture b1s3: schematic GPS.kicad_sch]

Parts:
BT1: Battery_Cell; BatteryHolder_Seiko_MS621F; Mfr. part number MS621FE-FL11E
C17, C18, C23, C27: 100nF; C_0603_1608Metric; Mfr. part number 06035C104KAZ4A; JLCPCB Part C14663
C19, C26: 10uF; C_0603_1608Metric; Mfr. part number GRM188Z71A106KA73D; JLCPCB Part C19702
C20, C21, C24: 10nF; C_0603_1608Metric; Mfr. part number SH18B103K160CT; JLCPCB Part C57112
C22, C25: 1uF; C_0603_1608Metric; Mfr. part number 885012206052; JLCPCB Part C15849
C28: 47pF; C_0603_1608Metric; Mfr. part number 06033C470KAT2A; JLCPCB Part C23345
D12: SP4020; D_SOD-323; Mfr. part number SP4020-01FTG-C; JLCPCB Part C126842
D28: PMEG10020; D_SOD-123F; Mfr. part number PMEG10020ELR-QX; JLCPCB Part C8597
FB3: FerriteBead; L_0805_2012Metric; Mfr. part number BLM21SP601SN1D; JLCPCB Part C3716677
FL1: B39162B3520U410; Mfr. part number B39162B3520U410; JLCPCB Part C2650959
J2: GPS antenna; SMA_Samtec_SMA-J-P-H-ST-EM1_EdgeMount; Mfr. part number SMA-J-P-H-ST-EM1; JLCPCB Part C5199907
L1: 27nH; L_0603_1608Metric; Mfr. part number LQW18AN27NJ00D; JLCPCB Part C98072
R56, R57, R58, R61: 1k; R_0603_1608Metric; Mfr. part number AC0603DR-071KL; JLCPCB Part C21190
R59, R60: 10k; R_0603_1608Metric; Mfr. part number CR0603-FX-1002ELF; JLCPCB Part C25804
R62: 390; R_0603_1608Metric; Mfr. part number RC0603FR-07390RP; JLCPCB Part C23151
SW3: GPS RESET; SW_Push_1P1T_NO_CK_KMR2; Mfr. part number PTS815SJM250SMTR LFS; JLCPCB Part C99271
U3: LDS3985M33R; SOT-23-5; Mfr. part number LDS3985M30R; JLCPCB Part C2970345
U4: PX1125R; PX1105R; Mfr. part number PX1105R; JLCPCB Part C9900164713

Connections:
+3.3V: C19.1, C20.1, D28.2 (A), R59.1, R60.1, U3.1 (IN); also elsewhere on the board
+3V3: C22.2, C23.2, C24.1, C26.1, U3.5 (OUT), U4.8 (VDD33)
/ESP32/ESP32_CS1: R56.1; also elsewhere on the board
/ESP32/ESP32_IO1: R61.1; also elsewhere on the board
/ESP32/ESP32_IO2: U4.4 (1PPS); also elsewhere on the board
/ESP32/ESP32_RXD1: R57.1; also elsewhere on the board
/ESP32/ESP32_TXD1: R58.1; also elsewhere on the board
/GPS/DIR/TRIG: U4.5 (DIR/TRIG); also elsewhere on the board
/GPS/RESET: C25.1, D12.1 (A1), R59.2, SW3.2, U4.9 (~RST)
/GPS/RXD2: R60.2, R61.2, U4.15 (RXD2)
/GPS/VCC_RF: C17.1, FB3.2, L1.1
/GPS/V_BAT: C27.1, D28.1 (K), R62.1, U4.6 (V_BCKP)
GND: BT1.2 (-), C17.2, C18.2, C19.2, C20.2, C21.2, C22.1, C23.1, C24.2, C25.2, C26.2, C27.2, D12.2 (A2), FL1.1 (GND_1), FL1.3 (GND_2), FL1.4 (GND_3), FL1.6 (GND_4), J2.2 (Ext), SW3.1, U3.2 (GND), U4.1 (GND), U4.10 (GND), U4.12 (GND); also elsewhere on the board
unnamed: BT1.1 (+), R62.2
unnamed: FL1.2 (INPUT), U4.11 (RF_IN)
unnamed: C28.1, FL1.5 (OUTPUT)
unnamed: C28.2, J2.1 (In), L1.2
unnamed: C21.1, U3.4 (Bypass)
unnamed: R56.2, U3.3 (EN)
unnamed: R58.2, U4.3 (RXD)
unnamed: R57.2, U4.2 (TXD)
unnamed: C18.1, FB3.1, U4.14 (VCC_RF)

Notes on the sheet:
RXD1: UART serial data input, 3.3V LVTTL. One full-duplex asynchronous serial UART port is implemented. This UART input is normally for sending commands or information to the receiver in SkyTraq binary protocol. In the idle condition, this pin should be driven HIGH. If the driving circuitry is powe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
TXD: UART serial data output, 3.3V LVTTL. One full-duplex asynchronous serial UART port is implemented. This UART output is normally used for sending position, time and velocity information from the receiver in NMEA-0183 format. When idle, this pin output HIGH.
RXD2: UART serial data input, 3.3V LVTTL. One simplex asynchronous serial UART port is implemented. This UART input is normally for sending RTCM-SC104 correction data or base station SkyTraq raw measurement data to the receiver at 115200 baud rate. In the idle condition, this pin should be driven H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
